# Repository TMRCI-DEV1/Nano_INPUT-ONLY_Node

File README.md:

# Nano_INPUT-ONLY_Node
Arduino Nano-based input only Node

Shield: [![CC BY-SA 4.0][cc-by-sa-shield]][cc-by-sa]

This work is licensed under a
[Creative Commons Attribution-ShareAlike 4.0 International License][cc-by-sa].

[![CC BY-SA 4.0][cc-by-sa-image]][cc-by-sa]

[cc-by-sa]: http://creativecommons.org/licenses/by-sa/4.0/
[cc-by-sa-image]: https://licensebuttons.net/l/by-sa/4.0/88x31.png
[cc-by-sa-shield]: https://img.shields.io/badge/License-CC%20BY--SA%204.0-lightgrey.svg

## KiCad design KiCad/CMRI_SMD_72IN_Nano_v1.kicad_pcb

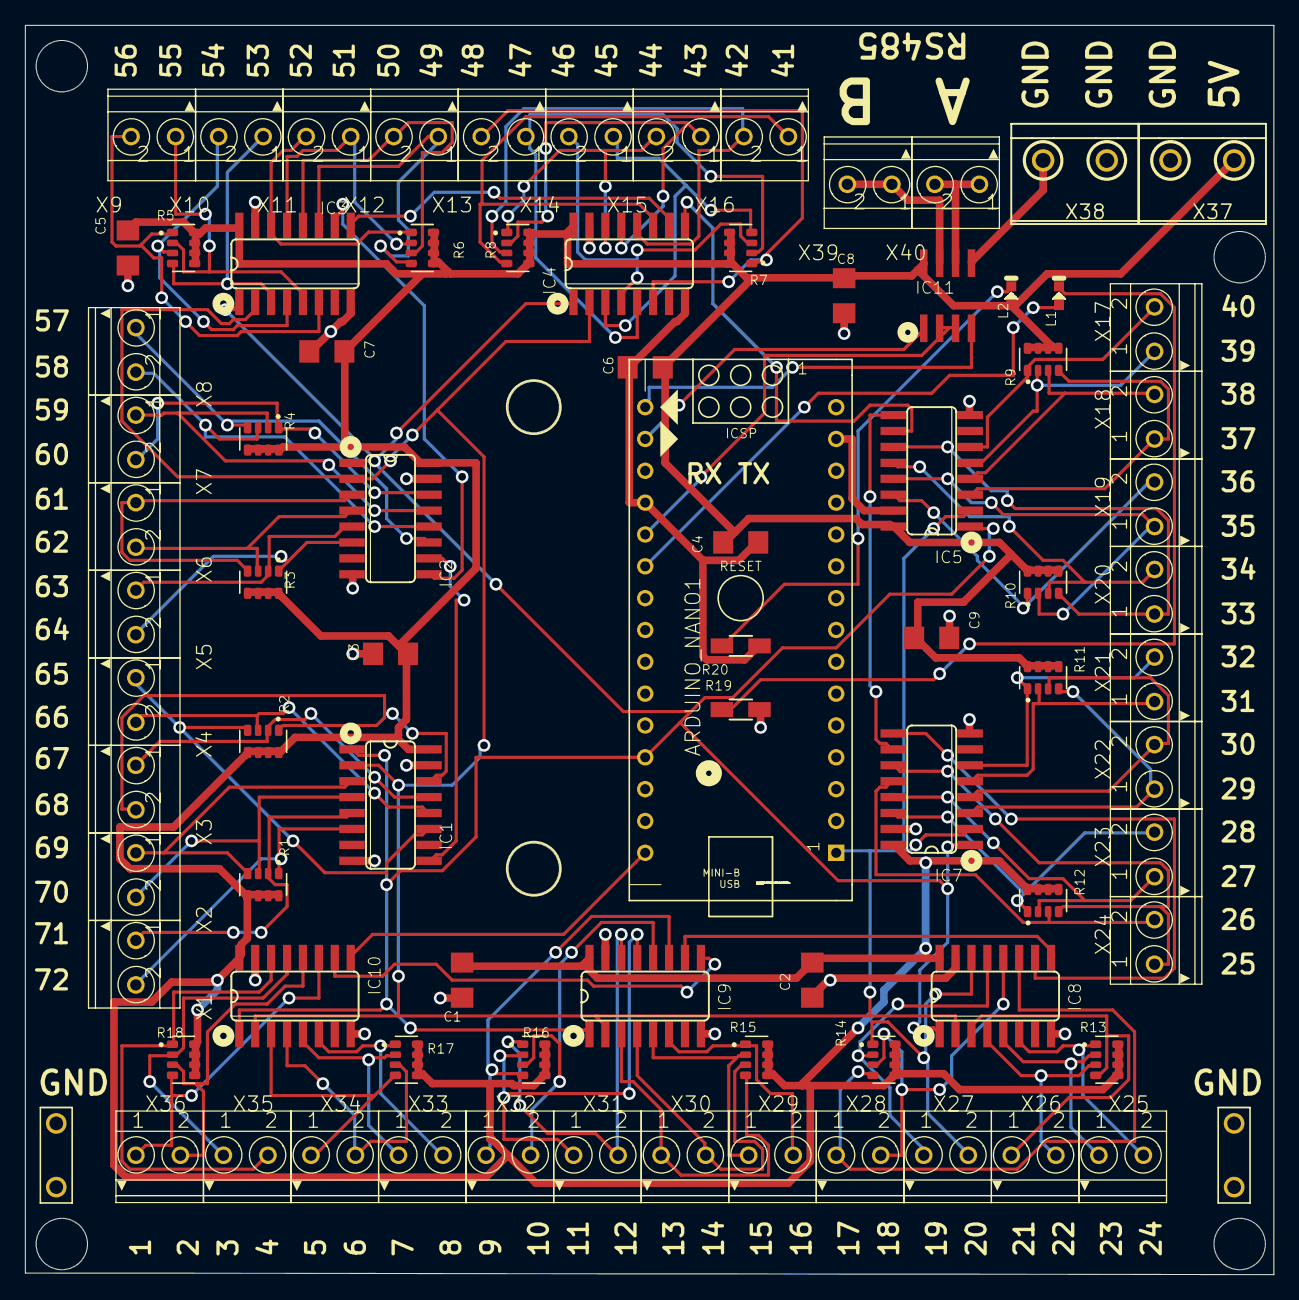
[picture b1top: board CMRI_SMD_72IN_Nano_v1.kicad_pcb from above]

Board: 2 copper layers, 99.6 x 99.7 mm, 86 parts (0 on the bottom side), 93 nets.

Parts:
ARDUINO_NANO1: ARDUINO_NANO
C1, C2, C3, C4, C5, C6, C7, C8, C9: 100nF; 1206
H1, H2: MOUNT-HOLE4.1; 4,1
IC1, IC2, IC3, IC4, IC5, IC7, IC8, IC9, IC10: 74HC165D; SO16
IC11: MAX485; SO08
L1: STATUS; LED-0603
L2: Vcc; LED-0603
R1, R2, R3, R4, R5, R6, R7, R8, R9, R10, R11, R12, R13, R14, R15, R16, R17, R18: 10k; RESISTORARRAY-0603
R19, R20: 1k; R1206W
U$1, U$2: LUG-5MM
X1, X2, X3, X4, X5, X6, X7, X8, X9, X10, X11, X12, X13, X14, X15, X16, X17, X18, X19, X20, X21, X22, X23, X24, X25, X26, X27, X28, X29, X30, X31, X32, X33, X34, X35, X36, X39, X40: TERMINAL_2P_3,5MM_V2
X37, X38: W237-132

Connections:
A: IC11.6, X40.P$1, X40.P$2
B: IC11.7, X39.P$1, X39.P$2
D3: ARDUINO_NANO1.21, L1.A
GND: ARDUINO_NANO1.14, ARDUINO_NANO1.19, C1.1, C2.1, C3.1, C4.1, C5.1, C6.1, C7.1, C8.1, C9.1, IC1.8, IC1.15, IC2.8, IC2.15, IC3.8, IC3.15, IC4.8, IC4.15, IC5.8, IC5.15, IC7.8, IC7.15, IC8.8, IC8.15, IC9.8, IC9.15, IC10.8, IC10.15, IC11.5, R19.1, R20.1, U$1.P$3, U$1.P$4, U$2.P$3, U$2.P$4, X37.2, X38.1, X38.2
LATCH: ARDUINO_NANO1.27, IC1.1, IC2.1, IC3.1, IC4.1, IC5.1, IC7.1, IC8.1, IC9.1, IC10.1
unnamed: IC3.11, R6.4, X12.P$1
unnamed: IC1.9, IC2.10
unnamed: IC3.12, R6.3, X12.P$2
unnamed: IC2.9, IC3.10
unnamed: IC3.13, R6.2, X11.P$1
unnamed: IC4.11, R8.4, X16.P$1
unnamed: IC3.14, R6.1, X11.P$2
unnamed: IC4.12, R8.3, X16.P$2
unnamed: IC3.3, R5.4, X10.P$1
unnamed: IC4.13, R8.2, X15.P$1
unnamed: IC3.4, R5.3, X10.P$2
unnamed: IC4.14, R8.1, X15.P$2
unnamed: IC3.5, R5.2, X9.P$1
unnamed: IC4.3, R7.4, X14.P$1
unnamed: IC3.6, R5.1, X9.P$2
unnamed: IC4.4, R7.3, X14.P$2
unnamed: L1.C, R19.2
unnamed: IC4.5, R7.2, X13.P$1
unnamed: IC2.11, R4.4, X8.P$1
unnamed: IC4.6, R7.1, X13.P$2
unnamed: IC2.12, R4.3, X8.P$2
unnamed: IC3.9, IC4.10
unnamed: IC2.13, R4.2, X7.P$1
unnamed: IC5.11, R10.4, X20.P$1
unnamed: IC2.14, R4.1, X7.P$2
unnamed: IC5.12, R10.3, X20.P$2
unnamed: IC2.3, R3.4, X6.P$1
unnamed: IC5.13, R10.2, X19.P$1
unnamed: IC2.4, R3.3, X6.P$2
unnamed: IC5.14, R10.1, X19.P$2
unnamed: IC2.5, R3.2, X5.P$1
unnamed: IC5.3, R9.4, X18.P$1
unnamed: IC2.6, R3.1, X5.P$2
unnamed: IC5.4, R9.3, X18.P$2
unnamed: IC1.11, R2.4, X4.P$1
unnamed: IC5.5, R9.2, X17.P$1
unnamed: IC1.12, R2.3, X4.P$2
unnamed: IC5.6, R9.1, X17.P$2
unnamed: IC1.13, R2.2, X3.P$1
unnamed: IC4.9, IC5.10
unnamed: IC1.14, R2.1, X3.P$2
unnamed: IC7.11, R12.4, X24.P$1
unnamed: IC1.3, R1.4, X2.P$1
unnamed: IC7.12, R12.3, X24.P$2
unnamed: IC1.4, R1.3, X2.P$2
unnamed: IC7.13, R12.2, X23.P$1
unnamed: IC1.5, R1.2, X1.P$1
unnamed: IC7.14, R12.1, X23.P$2
unnamed: IC7.3, R11.4, X22.P$1
unnamed: IC7.4, R11.3, X22.P$2
unnamed: IC7.5, R11.2, X21.P$1
unnamed: IC7.6, R11.1, X21.P$2
unnamed: IC5.9, IC7.10
unnamed: L2.C, R20.2
unnamed: ARDUINO_NANO1.20, IC11.2, IC11.3
unnamed: IC8.11, R14.4, X28.P$1
unnamed: IC1.6, R1.1, X1.P$2
unnamed: IC8.12, R14.3, X28.P$2
unnamed: IC8.13, R14.2, X27.P$1
unnamed: IC8.14, R14.1, X27.P$2
unnamed: IC8.3, R13.4, X26.P$1
unnamed: IC8.4, R13.3, X26.P$2
unnamed: IC8.5, R13.2, X25.P$1
unnamed: IC8.6, R13.1, X25.P$2
unnamed: IC7.9, IC8.10
unnamed: IC9.11, R16.4, X32.P$1
unnamed: IC9.12, R16.3, X32.P$2
unnamed: IC9.13, R16.2, X31.P$1
unnamed: IC9.14, R16.1, X31.P$2
unnamed: IC9.3, R15.4, X30.P$1
unnamed: IC9.4, R15.3, X30.P$2
unnamed: IC9.5, R15.2, X29.P$1
unnamed: IC9.6, R15.1, X29.P$2
unnamed: IC8.9, IC9.10
unnamed: IC10.11, R18.4, X36.P$1
unnamed: IC10.12, R18.3, X36.P$2
unnamed: IC10.13, R18.2, X35.P$1
unnamed: IC10.14, R18.1, X35.P$2
unnamed: IC10.3, R17.4, X34.P$1
unnamed: IC10.4, R17.3, X34.P$2
unnamed: IC10.5, R17.2, X33.P$1
unnamed: IC10.6, R17.1, X33.P$2
unnamed: IC9.9, IC10.10
RX: ARDUINO_NANO1.17, IC11.1
SCK: ARDUINO_NANO1.1, IC1.2, IC2.2, IC3.2, IC4.2, IC5.2, IC7.2, IC8.2, IC9.2, IC10.2
SO: ARDUINO_NANO1.30, IC10.9
TX: ARDUINO_NANO1.16, IC11.4
VCC: C1.2, C2.2, C3.2, C4.2, C5.2, C6.2, C7.2, C8.2, C9.2, IC1.16, IC2.16, IC3.16, IC4.16, IC5.16, IC7.16, IC8.16, IC9.16, IC10.16, IC11.8, L2.A, R1.5, R1.6, R1.7, R1.8, R2.5, R2.6, R2.7, R2.8, R3.5, R3.6, R3.7, R3.8, R4.5, R4.6, R4.7, R4.8, R5.5, R5.6, R5.7, R5.8, R6.5, R6.6, R6.7, R6.8, R7.5, R7.6, R7.7, R7.8, R8.5, R8.6, R8.7, R8.8, R9.5, R9.6, R9.7, R9.8, R10.5, R10.6, R10.7, R10.8, R11.5, R11.6, R11.7, R11.8, R12.5, R12.6, R12.7, R12.8, R13.5, R13.6, R13.7, R13.8, R14.5, R14.6, R14.7, R14.8, R15.5, R15.6, R15.7, R15.8, R16.5, R16.6, R16.7, R16.8, R17.5, R17.6, R17.7, R17.8, R18.5, R18.6, R18.7, R18.8, X37.1

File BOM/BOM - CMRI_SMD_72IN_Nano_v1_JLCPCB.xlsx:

Comment | Designator | Footprint | JLCPCB Part #
Status，CHIPLED_0603, yellow | L1 | 0603 | C125095
100nF | C1,C2,C3,C4,C5,C6,C7,C8,C9 | 1206 | C24497
MAX485，SO08 | IC11 | SOP8 | C481667
10k | R1, R2, R3, R4, R5, R6, R7, R8, R9, R10, R11, R12, R13, R14, R15, R16, R17, R18 | 0603 | C102646 |  | C192513 |  | C2654027
74HC165D | IC1, IC2, IC3, IC4, IC5, IC7, IC8, IC9, IC10 | SOIC16_150MIL | C5613
TERMINAL_7.5X7.3MM_TM | X1,X2,X3,X4,X5,X6,X7,X8,X9,X10,X11,X12,X13,X14,X15,X16,X17,X18,X19,X20,X21,X22,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 | KF350-3.5-2P | C474892
Vcc，CHIPLED_0603, red | L2 | 0603 | C94869
1k | R19, R20 | 1206 | C4410
QUICK CONNECT TERMINAL | U$1,U$2 | PLUGIN | C499663
TERMINAL_10.16X8.1MM_TM | X37,X38 | TERMINAL_10.16X8.1MM_TM | C8269

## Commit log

2023-04-12 Added full project
2023-05-17 Update Current_OPT_INPUT_ONLY_Node.ino
    Added header
2023-05-23 Create LICENSE
2023-05-23 Update LICENSE
